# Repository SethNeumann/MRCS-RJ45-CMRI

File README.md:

# REPO NAME: EagleTemplate-new

## License: Creative Commons Attribution-NonCommercial-ShareAlike

This is the origianl CMRI Molex KK 156 to RJ45 board the John Plocher designed for Jay Beckham. 
The intent is better wire management on classic CMRI DIN/DOUT [24|32] boards. RJ45 cables can easily and
neatly be routed around to distribution points.

It turns out that 0.156 edge connectors (available from Acculites) can also be used in the MOLEX pads, allowing
for mular connections to Tortoise by Circuitron stall motors.

This September 2023 update is part of a file cleanup effort.

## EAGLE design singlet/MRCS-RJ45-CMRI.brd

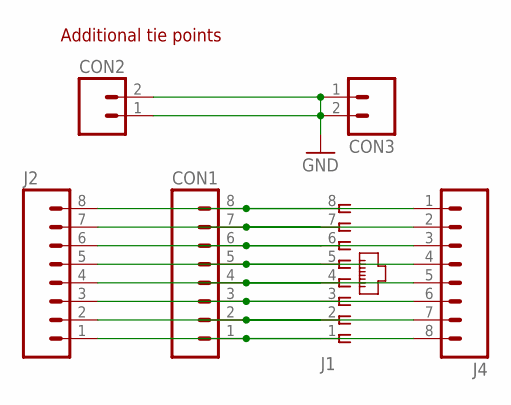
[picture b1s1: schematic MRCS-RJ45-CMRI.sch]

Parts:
CON1: CONNECTOR-M08LOCK; 1X08_LOCK
CON2, CON3: CONNECTOR-M023.5MM-LOCK; SCREWTERMINAL-3.5MM-2_LOCK
J1: CONNECTOR-RJ45-FRONT; RJ45-NO-SHIELD
J2: CONNECTOR-M083.5MM-8; SCREWTERMINAL-3.5MM-8
J4: CONNECTOR-M081.56-F; KK-156-8-F

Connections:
GND: CON2.1 (A), CON2.2 (B), CON3.1 (A), CON3.2 (B)
L1: CON1.1, J1.1, J2.1, J4.8
L2: CON1.2, J1.2, J2.2, J4.7
L3: CON1.3, J1.3, J2.3, J4.6
L4: CON1.4, J1.4, J2.4, J4.5
L5: CON1.5, J1.5, J2.5, J4.4
L6: CON1.6, J1.6, J2.6, J4.3
L7: CON1.7, J1.7, J2.7, J4.2
L8: CON1.8, J1.8, J2.8, J4.1

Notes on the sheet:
Additional tie points

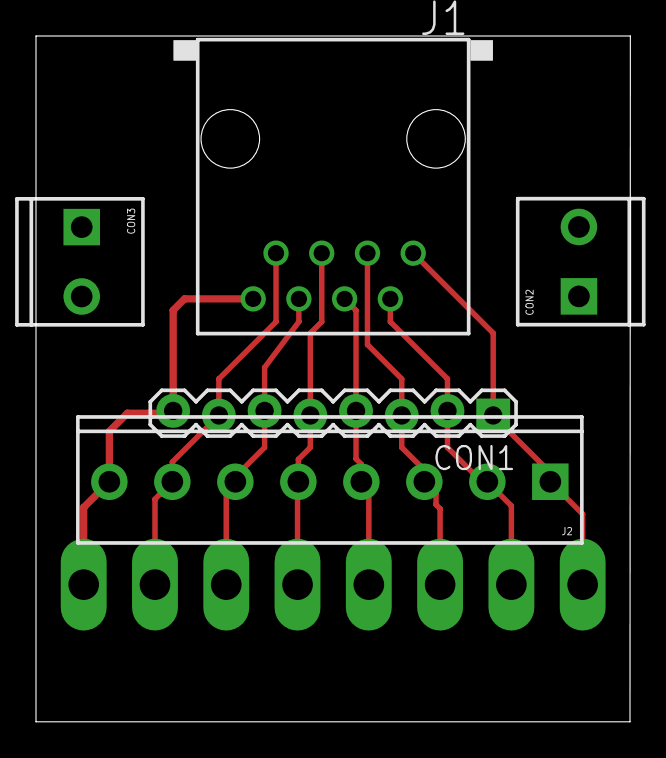
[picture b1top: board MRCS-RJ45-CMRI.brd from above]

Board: 2 copper layers, 33.0 x 38.1 mm, 7 parts (1 on the bottom side), 9 nets.

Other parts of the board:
U$1: MRCSLOGOBTM

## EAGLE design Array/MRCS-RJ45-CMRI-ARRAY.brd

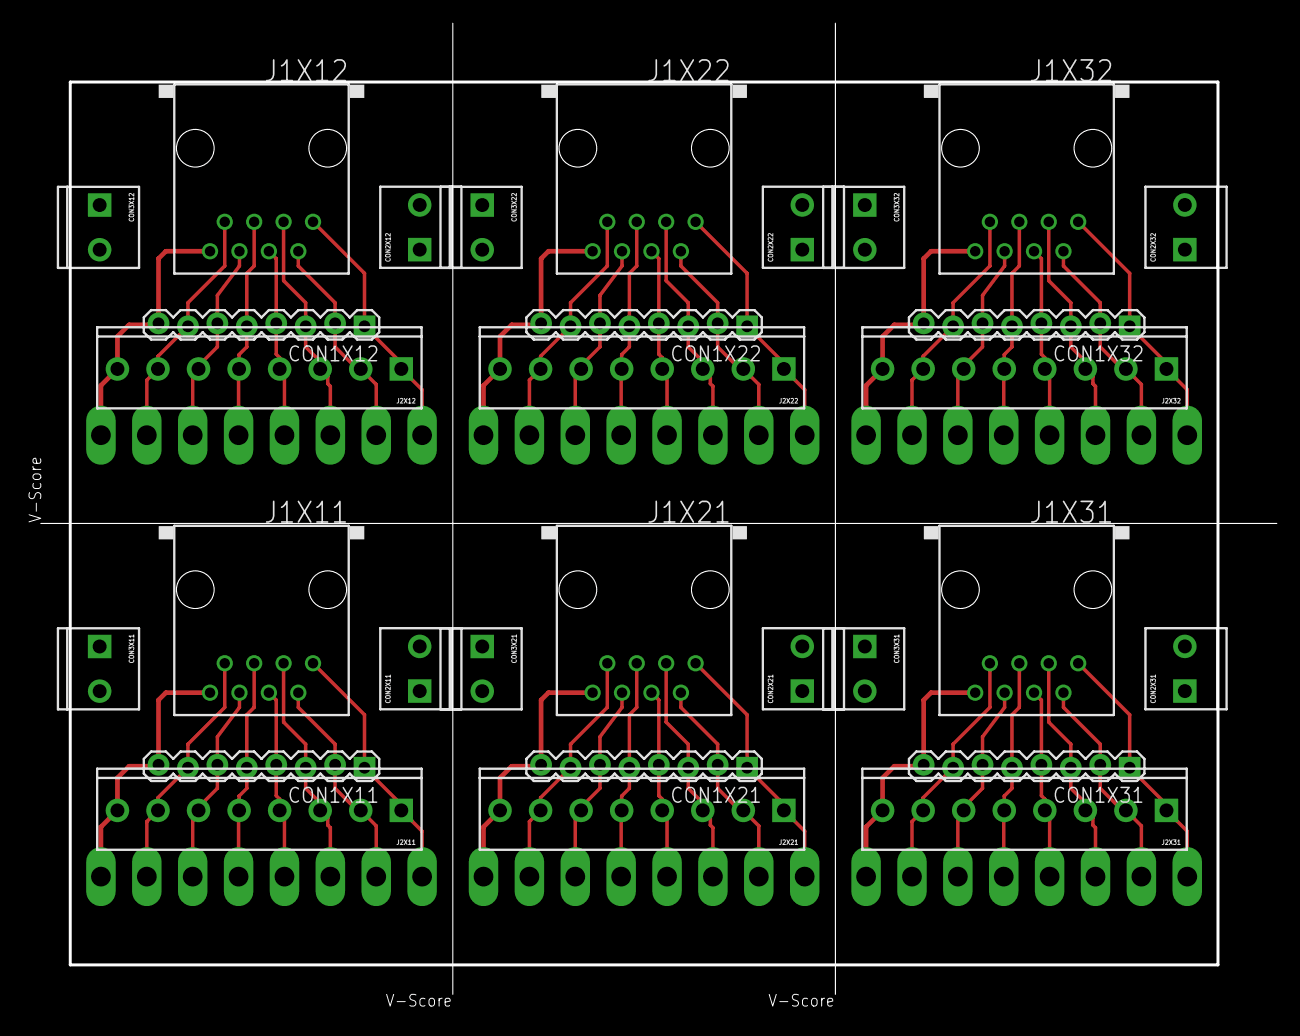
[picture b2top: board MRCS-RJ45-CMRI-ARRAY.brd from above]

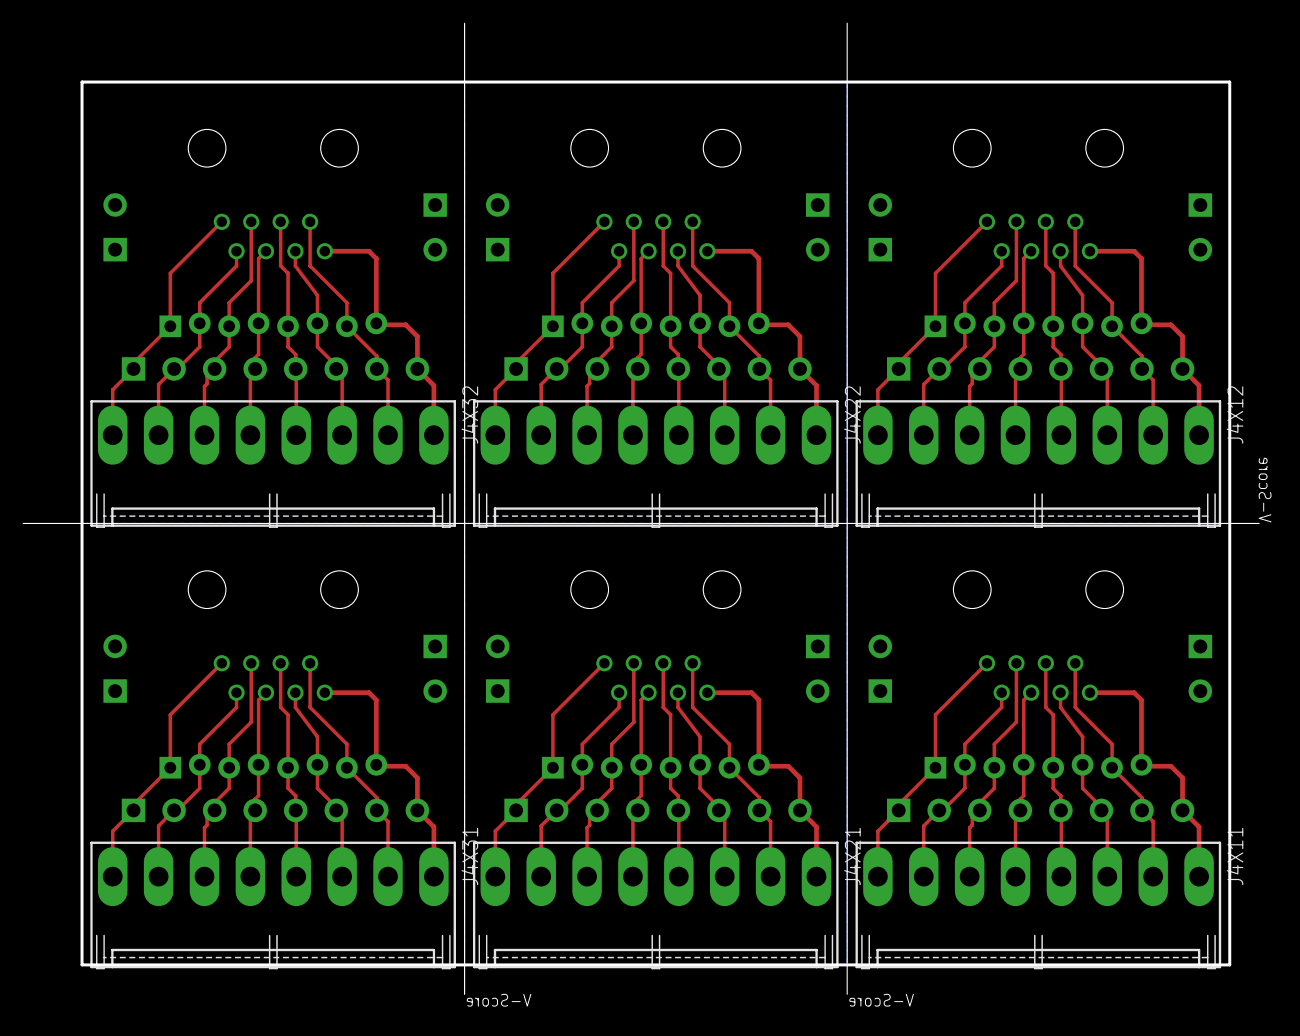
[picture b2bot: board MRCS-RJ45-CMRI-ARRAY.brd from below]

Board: 2 copper layers, 106.7 x 83.8 mm, 42 parts (6 on the bottom side), 54 nets.

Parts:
CON1X11, CON1X12, CON1X21, CON1X22, CON1X31, CON1X32: 1X08_LOCK
CON2X11, CON2X12, CON2X21, CON2X22, CON2X31, CON2X32, CON3X11, CON3X12, CON3X21, CON3X22, CON3X31, CON3X32: SCREWTERMINAL-3.5MM-2_LOCK
J1X11, J1X12, J1X21, J1X22, J1X31, J1X32: RJ45-NO-SHIELD
J2X11, J2X12, J2X21, J2X22, J2X31, J2X32: SCREWTERMINAL-3.5MM-8
J4X11, J4X12, J4X21, J4X22, J4X31, J4X32: KK-156-8-F
U$1X11, U$1X12, U$1X21, U$1X22, U$1X31, U$1X32: MRCSLOGOBTM

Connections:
GNDX11: CON2X11.1, CON2X11.2, CON3X11.1, CON3X11.2
GNDX12: CON2X12.1, CON2X12.2, CON3X12.1, CON3X12.2
GNDX21: CON2X21.1, CON2X21.2, CON3X21.1, CON3X21.2
GNDX22: CON2X22.1, CON2X22.2, CON3X22.1, CON3X22.2
GNDX31: CON2X31.1, CON2X31.2, CON3X31.1, CON3X31.2
GNDX32: CON2X32.1, CON2X32.2, CON3X32.1, CON3X32.2
L1X11: CON1X11.1, J1X11.1, J2X11.1, J4X11.8
L1X12: CON1X12.1, J1X12.1, J2X12.1, J4X12.8
L1X21: CON1X21.1, J1X21.1, J2X21.1, J4X21.8
L1X22: CON1X22.1, J1X22.1, J2X22.1, J4X22.8
L1X31: CON1X31.1, J1X31.1, J2X31.1, J4X31.8
L1X32: CON1X32.1, J1X32.1, J2X32.1, J4X32.8
L2X11: CON1X11.2, J1X11.2, J2X11.2, J4X11.7
L2X12: CON1X12.2, J1X12.2, J2X12.2, J4X12.7
L2X21: CON1X21.2, J1X21.2, J2X21.2, J4X21.7
L2X22: CON1X22.2, J1X22.2, J2X22.2, J4X22.7
L2X31: CON1X31.2, J1X31.2, J2X31.2, J4X31.7
L2X32: CON1X32.2, J1X32.2, J2X32.2, J4X32.7
L3X11: CON1X11.3, J1X11.3, J2X11.3, J4X11.6
L3X12: CON1X12.3, J1X12.3, J2X12.3, J4X12.6
L3X21: CON1X21.3, J1X21.3, J2X21.3, J4X21.6
L3X22: CON1X22.3, J1X22.3, J2X22.3, J4X22.6
L3X31: CON1X31.3, J1X31.3, J2X31.3, J4X31.6
L3X32: CON1X32.3, J1X32.3, J2X32.3, J4X32.6
L4X11: CON1X11.4, J1X11.4, J2X11.4, J4X11.5
L4X12: CON1X12.4, J1X12.4, J2X12.4, J4X12.5
L4X21: CON1X21.4, J1X21.4, J2X21.4, J4X21.5
L4X22: CON1X22.4, J1X22.4, J2X22.4, J4X22.5
L4X31: CON1X31.4, J1X31.4, J2X31.4, J4X31.5
L4X32: CON1X32.4, J1X32.4, J2X32.4, J4X32.5
L5X11: CON1X11.5, J1X11.5, J2X11.5, J4X11.4
L5X12: CON1X12.5, J1X12.5, J2X12.5, J4X12.4
L5X21: CON1X21.5, J1X21.5, J2X21.5, J4X21.4
L5X22: CON1X22.5, J1X22.5, J2X22.5, J4X22.4
L5X31: CON1X31.5, J1X31.5, J2X31.5, J4X31.4
L5X32: CON1X32.5, J1X32.5, J2X32.5, J4X32.4
L6X11: CON1X11.6, J1X11.6, J2X11.6, J4X11.3
L6X12: CON1X12.6, J1X12.6, J2X12.6, J4X12.3
L6X21: CON1X21.6, J1X21.6, J2X21.6, J4X21.3
L6X22: CON1X22.6, J1X22.6, J2X22.6, J4X22.3
L6X31: CON1X31.6, J1X31.6, J2X31.6, J4X31.3
L6X32: CON1X32.6, J1X32.6, J2X32.6, J4X32.3
L7X11: CON1X11.7, J1X11.7, J2X11.7, J4X11.2
L7X12: CON1X12.7, J1X12.7, J2X12.7, J4X12.2
L7X21: CON1X21.7, J1X21.7, J2X21.7, J4X21.2
L7X22: CON1X22.7, J1X22.7, J2X22.7, J4X22.2
L7X31: CON1X31.7, J1X31.7, J2X31.7, J4X31.2
L7X32: CON1X32.7, J1X32.7, J2X32.7, J4X32.2
L8X11: CON1X11.8, J1X11.8, J2X11.8, J4X11.1
L8X12: CON1X12.8, J1X12.8, J2X12.8, J4X12.1
L8X21: CON1X21.8, J1X21.8, J2X21.8, J4X21.1
L8X22: CON1X22.8, J1X22.8, J2X22.8, J4X22.1
L8X31: CON1X31.8, J1X31.8, J2X31.8, J4X31.1
L8X32: CON1X32.8, J1X32.8, J2X32.8, J4X32.1

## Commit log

2023-09-03 Initial Commit
    needed to make more and files were in an old directory
2023-09-03 intial commit
2023-09-03 moving file around
    moving existing files into Github
2023-09-13 Repanelized after old version lost
